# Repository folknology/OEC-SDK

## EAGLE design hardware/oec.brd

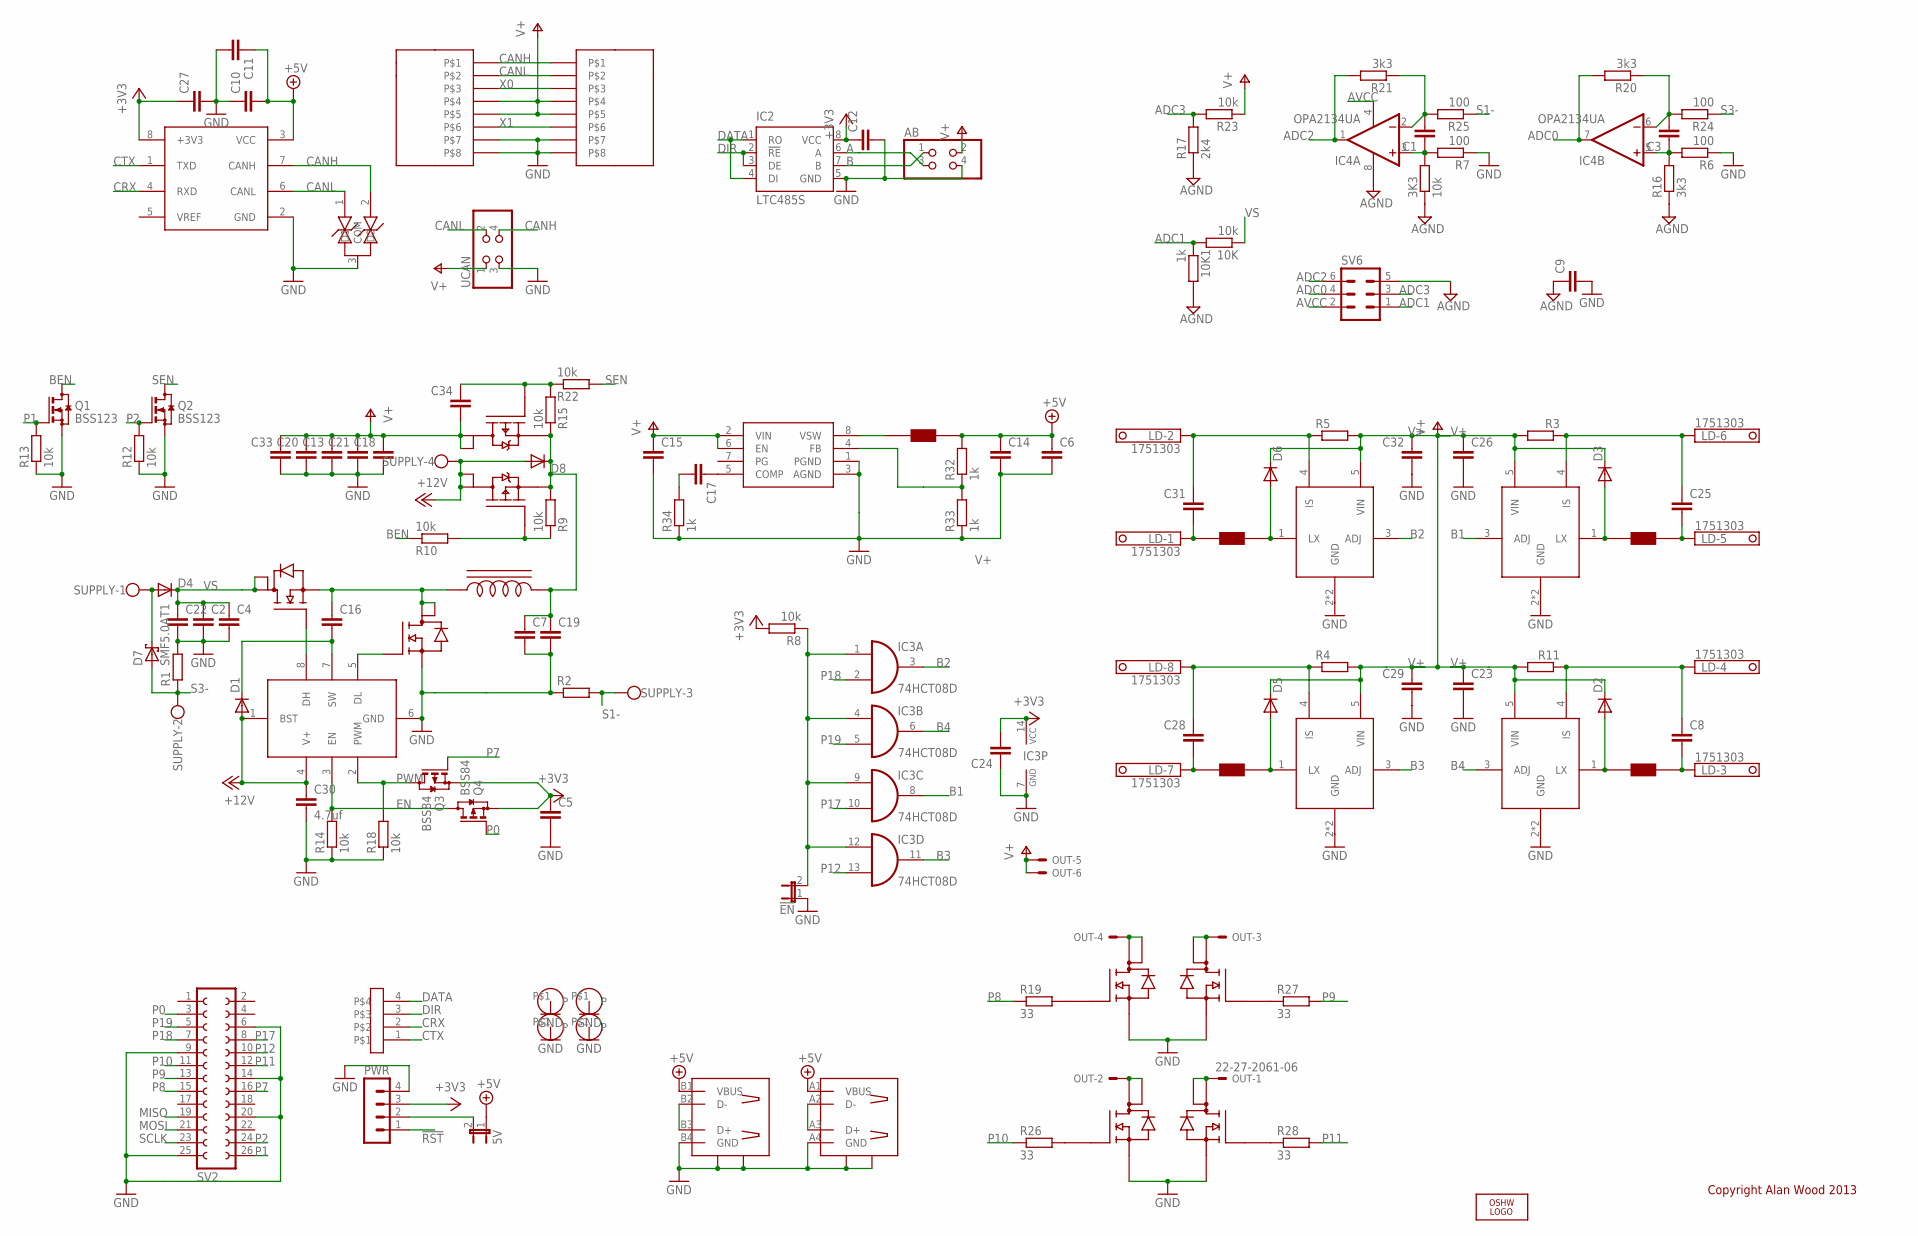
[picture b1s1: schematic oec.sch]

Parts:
3K3, 10K: 10k; R0805
5V: JP1E; JP1
10K1: 1k; R0805
!EN: JP1E; JP1
AB: PINHD-2X2/90; 2X02/90
C1, C3, C5, C9, C12, C15, C16, C17, C24, C27, C34: C-EUC0805; C0805
C2, C4, C6, C7, C8, C10, C11, C13, C14, C18, C19, C20, C21, C22, C23, C25, C26, C28, C29, C31, C32, C33: C-EUC1210; C1210
C30: 4.7uf; C0805
COM: 4X1X2.54-HEADER; 2.54_HEADER_4W
D1, D2, D3, D5, D6: DIODE-SOD123; SOD123
D4, D8: DIODE-DO214AC; DO214AC
D7: SMF5.0AT1; SOD123FL
IC2: LTC485S; SOIC8
IC3: 74HCT08D; SO14
IC4: OPA2134UA; SO08
LD: 1751303
LOGO1: OSHW_LOGO_FILLX0200-NT; OSHW_FILLX200_NOTEXT
OUT: 22-27-2061-06; 6410-06
PWR: MA04-1
Q1, Q2: BSS123; SOT23
Q3, Q4: BSS84; SOT23
R1, R2: R-EU_R1206; R1206
R3, R4, R5, R11: R-EU_R1210; R1210
R6, R7, R24, R25: 100; R0805
R8, R9, R10, R12, R13, R14, R15, R18, R22, R23: 10k; R0805
R16, R20, R21: 3k3; R0805
R17: 2k4; R0805
R19, R26, R27, R28: 33; R0603
R32, R33, R34: 1k; R0805
SUPPLY: W237-4
SV2: FE13-2
SV6: MA03-2
U$1, U$2, U$3, U$4: HOLE-2.5MM; 2.5MM-HOLE
U$5: NCP3170SOIC-8; SOIC-8-NARROW
U$6, U$8: NTMD4820NR2G; SOIC-8-NARROW
U$7: AMIS-3063; SOIC-8-NARROW
U$9: NRS6045T330MMGK; TAIKO-YUDEN-6045
U$12: NCP3420; SO8
U$13, U$14: RJHSE-5080; RJ45
U$15: DR127-XXX; DR127
U$16: DUAL-USBA-PTH-5787617-1; DUAL-USBA-PTH
U$17: NUP2105L; SOT23
U$19: SI49255DD; SO8
U$20: IRF9358PBF; SO8
U$25, U$27, U$29, U$31: ZLED7X20; SOT89-5
U$33, U$34, U$35, U$36: NR5040T330M; TAIKO-YUDEN-5040
UCAN: PINHD-2X2; 2X02

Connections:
!RST: PWR.1
+3V3: C5.1, C12.1, C24.2, C27.1, IC2.8 (VCC), IC3.14 (VCC), PWR.3, Q3.2 (S), Q4.2 (S), R8.2, U$7.8 (+3V3)
+5V: 5V.1, C6.1, C10.2, C11.1, C14.1, R32.2, U$7.3 (VCC), U$9.2, U$16.A1 (VBUS), U$16.B1 (VBUS)
+12V: C30.1, D1.A, D8.A, SUPPLY.4, U$12.1 (BST), U$12.4 (V+), U$19.7 (D), U$19.8 (D)
A: AB.3, IC2.6 (A)
ADC0: IC4.7 (OUT), R20.2, SV6.4
ADC1: 10K.2, 10K1.1, SV6.1
ADC2: IC4.1 (OUT), R21.2, SV6.6
ADC3: R17.2, R23.2, SV6.3
AGND: 3K3.1, 10K1.2, C9.1, IC4.8 (V+), R16.1, R17.1, SV6.5
AVCC: IC4.4 (V-), SV6.2
B: AB.1, IC2.7 (B)
B1: IC3.8 (O), U$27.3 (ADJ)
B2: IC3.3 (O), U$31.3 (ADJ)
B3: IC3.11 (O), U$29.3 (ADJ)
B4: IC3.6 (O), U$25.3 (ADJ)
BATTEN: R9.1, R10.2, U$19.2 (G)
BEN: Q1.3 (D), R10.1
CANH: U$7.7 (CANH), U$13.P$1, U$14.P$1, U$17.2 (D2), UCAN.4
CANL: U$7.6 (CANL), U$13.P$2, U$14.P$2, U$17.1 (D1), UCAN.2
CRX: COM.2, U$7.4 (RXD)
CTX: COM.1, U$7.1 (TXD)
DATA: COM.4, IC2.1 (RO), IC2.4 (DI)
DIR: COM.3, IC2.2 (!RE), IC2.3 (DE)
EN: Q4.3 (D), R14.2, U$12.3 (EN)
GND: !EN.1, AB.4, C2.2, C4.2, C5.2, C6.2, C7.2, C9.2, C10.1, C11.2, C12.2, C13.2, C14.2, C15.2, C18.2, C19.2, C20.2, C21.2, C22.2, C23.2, C24.1, C26.2, C27.2, C29.2, C30.2, C32.2, C33.2, IC2.5 (GND), IC3.7 (GND), PWR.4, Q1.2 (S), Q2.2 (S), R1.2, R2.1, R6.1, R7.1, R12.1, R13.1, R14.1, R18.1, R33.1, R34.1, SV2.6, SV2.9, SV2.14, SV2.20, SV2.25, U$1.P$1, U$2.P$1, U$3.P$1, U$4.P$1, U$5.1 (PGND), U$5.3 (AGND), U$6.1 (S1), U$6.3 (S2), U$7.2 (GND), U$8.1 (S1), U$8.3 (S2), U$12.6 (GND), U$13.P$7, U$13.P$8, U$14.P$7, U$14.P$8, U$16.A4 (GND), U$16.B4 (GND), U$16.SH2B (SH), U$16.SH@1A (SH), U$16.SH@1B (SH), U$16.SH@2A (SH), U$17.3 (COM), U$20.3 (S), U$25.2 (GND), U$25.2@1 (GND), U$27.2 (GND), U$27.2@1 (GND), U$29.2 (GND), U$29.2@1 (GND), U$31.2 (GND), U$31.2@1 (GND), UCAN.3
ID: C16.1, U$15.P$1 (L1), U$20.1 (S), U$20.5 (D), U$20.6 (D)
MISO: SV2.19
MOSI: SV2.21
unnamed: C17.1, U$5.5 (COMP)
unnamed: !EN.2, IC3.1 (I0), IC3.4 (I0), IC3.9 (I0), IC3.12 (I0), R8.1
unnamed: D2.A, U$25.1 (LX), U$36.1
unnamed: R19.2, U$6.2 (G1)
unnamed: C8.2, LD.3, U$36.2
unnamed: U$5.8 (VSW), U$9.1
unnamed: OUT.4, U$6.7 (DP1), U$6.8 (D1)
unnamed: U$12.8 (DH), U$20.2 (G)
unnamed: R26.2, U$8.2 (G1)
unnamed: C8.1, LD.4, R11.1, U$25.4 (IS)
unnamed: D5.A, U$29.1 (LX), U$35.2
unnamed: U$12.5 (DL), U$20.4 (G)
unnamed: C16.2, D1.C, U$12.7 (SW)
unnamed: R28.1, U$8.4 (G2)
unnamed: OUT.3, U$6.5 (DP2), U$6.6 (D2)
unnamed: R27.1, U$6.4 (G2)
unnamed: OUT.2, U$8.7 (DP1), U$8.8 (D1)
unnamed: OUT.1, U$8.5 (DP2), U$8.6 (D2)
unnamed: U$16.B2 (D-), U$16.B3 (D+)
unnamed: R32.1, R33.2, U$5.4 (FB)
unnamed: U$16.A2 (D-), U$16.A3 (D+)
unnamed: D4.A, D7.C, SUPPLY.1
unnamed: 3K3.2, C1.1, IC4.3 (+IN), R7.2
unnamed: C3.1, IC4.5 (+IN), R6.2, R16.2
unnamed: C34.1, R15.2, R22.1, U$19.4 (G)
unnamed: D3.A, U$27.1 (LX), U$34.1
unnamed: C17.2, R34.2
unnamed: C25.2, LD.5, U$34.2
unnamed: C1.2, IC4.2 (-IN), R21.1, R25.2
unnamed: C3.2, IC4.6 (-IN), R20.1, R24.2
unnamed: C25.1, LD.6, R3.1, U$27.4 (IS)
unnamed: C28.2, LD.7, U$35.1
unnamed: C28.1, LD.8, R4.1, U$29.4 (IS)
unnamed: D6.A, U$31.1 (LX), U$33.2
unnamed: C31.2, LD.1, U$33.1
unnamed: C31.1, LD.2, R5.1, U$31.4 (IS)
P0: Q4.1 (G), SV2.3
P1: Q1.1 (G), R13.2, SV2.26
P2: Q2.1 (G), R12.2, SV2.24
P7: Q3.1 (G), SV2.16
P8: R19.1, SV2.15
P9: R27.2, SV2.13
P10: R26.1, SV2.11
P11: R28.2, SV2.12
P12: IC3.13 (I1), SV2.10
P17: IC3.10 (I1), SV2.8
P18: IC3.2 (I1), SV2.7
P19: IC3.5 (I1), SV2.5
PWM: Q3.3 (D), R18.2, U$12.2 (PWM)
S1-: R2.2, R25.1, SUPPLY.3
S3-: D7.A, R1.1, R24.1, SUPPLY.2
SCLK: SV2.23
SEN: Q2.3 (D), R22.2
V+: AB.2, C13.1, C15.1, C18.1, C20.1, C21.1, C23.1, C26.1, C29.1, C32.1, C33.1, C34.2, D2.C, D3.C, D5.C, D6.C, OUT.5, OUT.6, R3.2, R4.2, R5.2, R11.2, R23.1, U$5.2 (VIN), U$5.6 (EN), U$13.P$4, U$13.P$5, U$14.P$4, U$14.P$5, U$19.5 (D), U$19.6 (D), U$25.5 (VIN), U$27.5 (VIN), U$29.5 (VIN), U$31.5 (VIN), UCAN.1
VBUCK: C7.1, C19.1, D8.C, R9.2, R15.1, U$15.P$2 (L2), U$19.1 (S), U$19.3 (S)
VISB: 5V.2, PWR.2
VS: 10K.1, C2.1, C4.1, C22.1, D4.C, U$20.7 (D), U$20.8 (D)
X0: U$13.P$3, U$14.P$3
X1: U$13.P$6, U$14.P$6

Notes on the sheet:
Copyright Alan Wood 2013

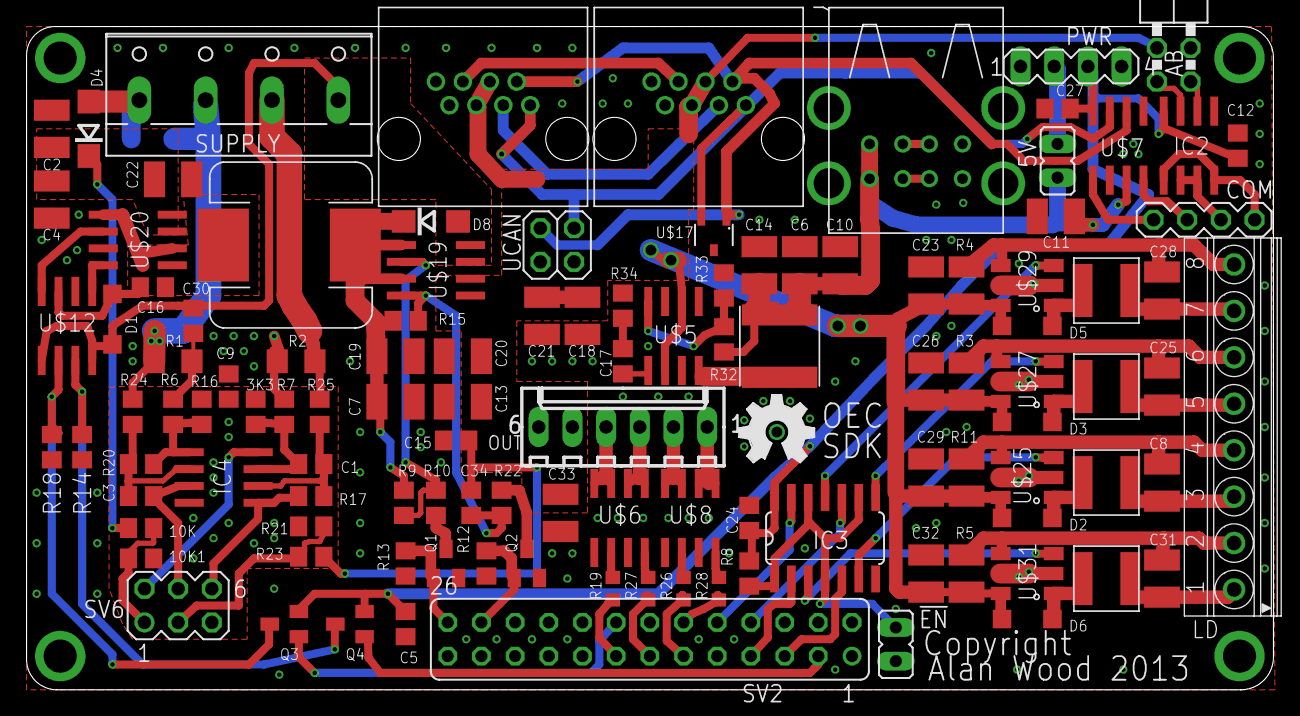
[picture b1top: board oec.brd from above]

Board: 2 copper layers, 94.0 x 50.0 mm, 120 parts (1 on the bottom side), 84 nets.

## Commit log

2013-11-23 Added OEC board and schematic
